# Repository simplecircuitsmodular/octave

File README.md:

# Sub Oscillator

This module features -1,-2, and -3 octave square wave outputs, selectable via a rotary switch. An input through jack allows the original signal to be passed on to other modules, while an attenuator and enable switch allow the sub oscillator to be easily added and removed from your mix.

## Files
### octave_xx .brd and .sch
These are the board and schematic files needed to manufacture PCBs. Gerbers need to be generated in Eagle for manufacturing.

### octaveParts_xx.md
These are the parts lists for each module. A mouser BOM is available in this file as well.

### octave.ai
This is the panel in Adobe Illustrator format. I make my panels on a laser cutter with 1/8 inch acrylic.

## Updates

### 01 07OCT19
Initial upload. The module is currently untested.

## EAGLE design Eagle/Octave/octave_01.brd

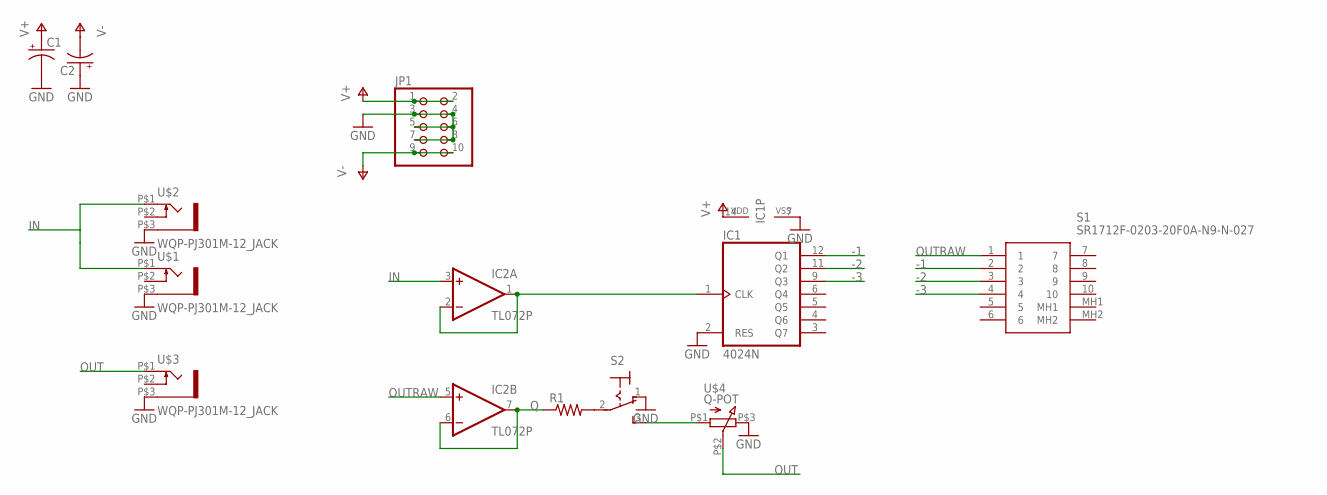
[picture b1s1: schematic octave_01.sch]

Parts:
C1, C2: CPOL-USE2-4; E2-4
IC1: 4024N; DIL14
IC2: TL072P; DIL08
JP1: PINHD-2X5/OCT; 2X05
R1: R-US_0204/7; 0204/7
S1: SR1712F-0203-20F0A-N9-N-027; SR1712F020320F0AN9N027
S2: M9040P
U$1, U$2, U$3: WQP-PJ301M-12_JACK
U$4: Q-POT

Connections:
-1: IC1.12 (Q1), S1.2
-2: IC1.11 (Q2), S1.3
-3: IC1.9 (Q3), S1.4
GND: C1.-, C2.+, IC1.2 (RES), IC1.7 (VSS), JP1.3, JP1.4, JP1.5, JP1.6, JP1.7, JP1.8, S2.1 (O), U$1.P$3 (1), U$2.P$3 (1), U$3.P$3 (1), U$4.P$3 (3)
IN: IC2.3 (+IN), U$1.P$1 (2), U$2.P$1 (2)
unnamed: IC1.1 (CLK), IC2.1 (OUT), IC2.2 (-IN)
unnamed: R1.2, S2.2, S2.3 (S), U$4.P$1 (1)
OUT: U$3.P$1 (2), U$4.P$2 (2)
OUTRAW: IC2.5 (+IN), S1.1
Q: IC2.6 (-IN), IC2.7 (OUT), R1.1
V+: C1.+, IC1.14 (VDD), IC2.8 (V+), JP1.1, JP1.2
V-: C2.-, IC2.4 (V-), JP1.9, JP1.10

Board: 2 copper layers, 12 parts (6 on the bottom side), 12 nets, no tracks yet.

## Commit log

2019-10-07 Add panel outline
